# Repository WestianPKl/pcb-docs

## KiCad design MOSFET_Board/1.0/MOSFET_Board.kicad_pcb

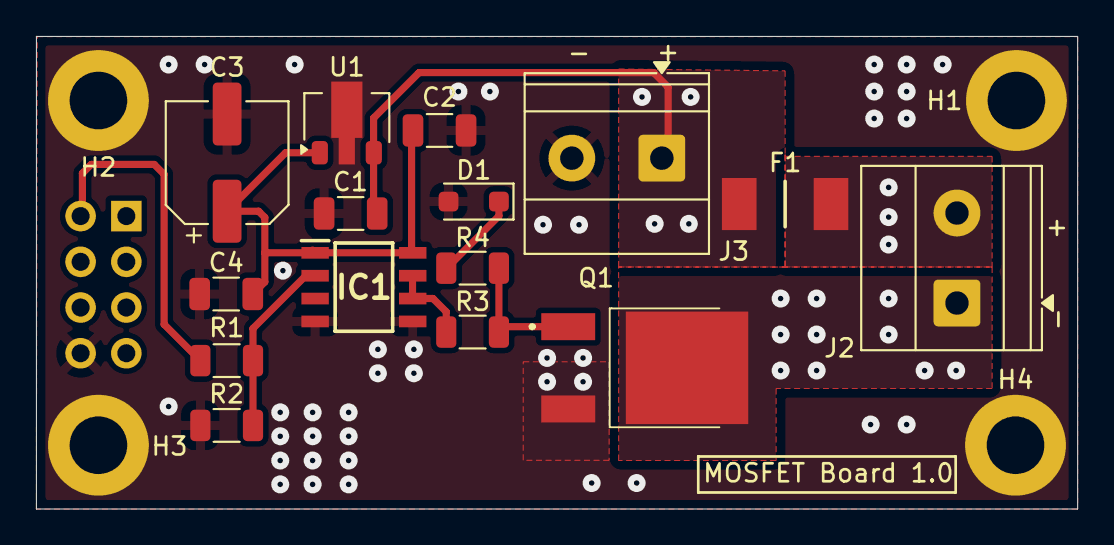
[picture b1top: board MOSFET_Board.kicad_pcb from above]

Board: 2 copper layers, 57.8 x 26.3 mm, 20 parts (1 on the bottom side), 10 nets.

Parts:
C1: 330nF; C_1206_3216Metric
C2, C4: 100nF; C_1206_3216Metric
C3: 10uF; CP_Elec_6.3x5.8
D1: BZT52C15-DIO; D_SOD-123F
F1: TR1-2410TD5-R; FUSC6127X287N
H1, H2, H3, H4: MountingHole_Pad; MountingHole_3.2mm_M3_DIN965_Pad
IC1: TC4420EOA; SOIC127P600X175-8N
J1: COM; PinHeader_2x04_P2.54mm_Vertical
J2: BULB; TerminalBlock_Phoenix_MKDS-1,5-2_1x02_P5.00mm_Horizontal
J3: PWR; TerminalBlock_Phoenix_MKDS-1,5-2_1x02_P5.00mm_Horizontal
Q1: AOD4184A; AOD4185
R1: 100R; R_1206_3216Metric
R2: 47K; R_1206_3216Metric
R3: 10R; R_1206_3216Metric
R4: 100K; R_1206_3216Metric
U1: L78L12ABUTR; SOT-89-3

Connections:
+12V: C1.1, F1.2, J3.1, U1.3 (IN)
+12V_STAB: C2.1, C3.1, C4.1, IC1.1 (VDD_1), IC1.8 (VDD_2), U1.1 (OUT)
GND: C1.2, C2.2, C3.2, C4.2, D1.2 (A), H1.1, H2.1, H3.1, H4.1, IC1.4 (GND_1), IC1.5 (GND_2), J1.8, J3.2, Q1.3 (S), R2.2, U1.2 (GND)
unnamed: D1.1 (K), R4.2
unnamed: IC1.2 (INPUT), R1.2, R2.1
unnamed: IC1.6 (OUTPUT_1), IC1.7 (OUTPUT_2), R3.1
unnamed: J1.2, R1.1
unnamed: J2.1, Q1.2 (D)
unnamed: F1.1, J2.2
unnamed: Q1.1 (G), R3.2, R4.1

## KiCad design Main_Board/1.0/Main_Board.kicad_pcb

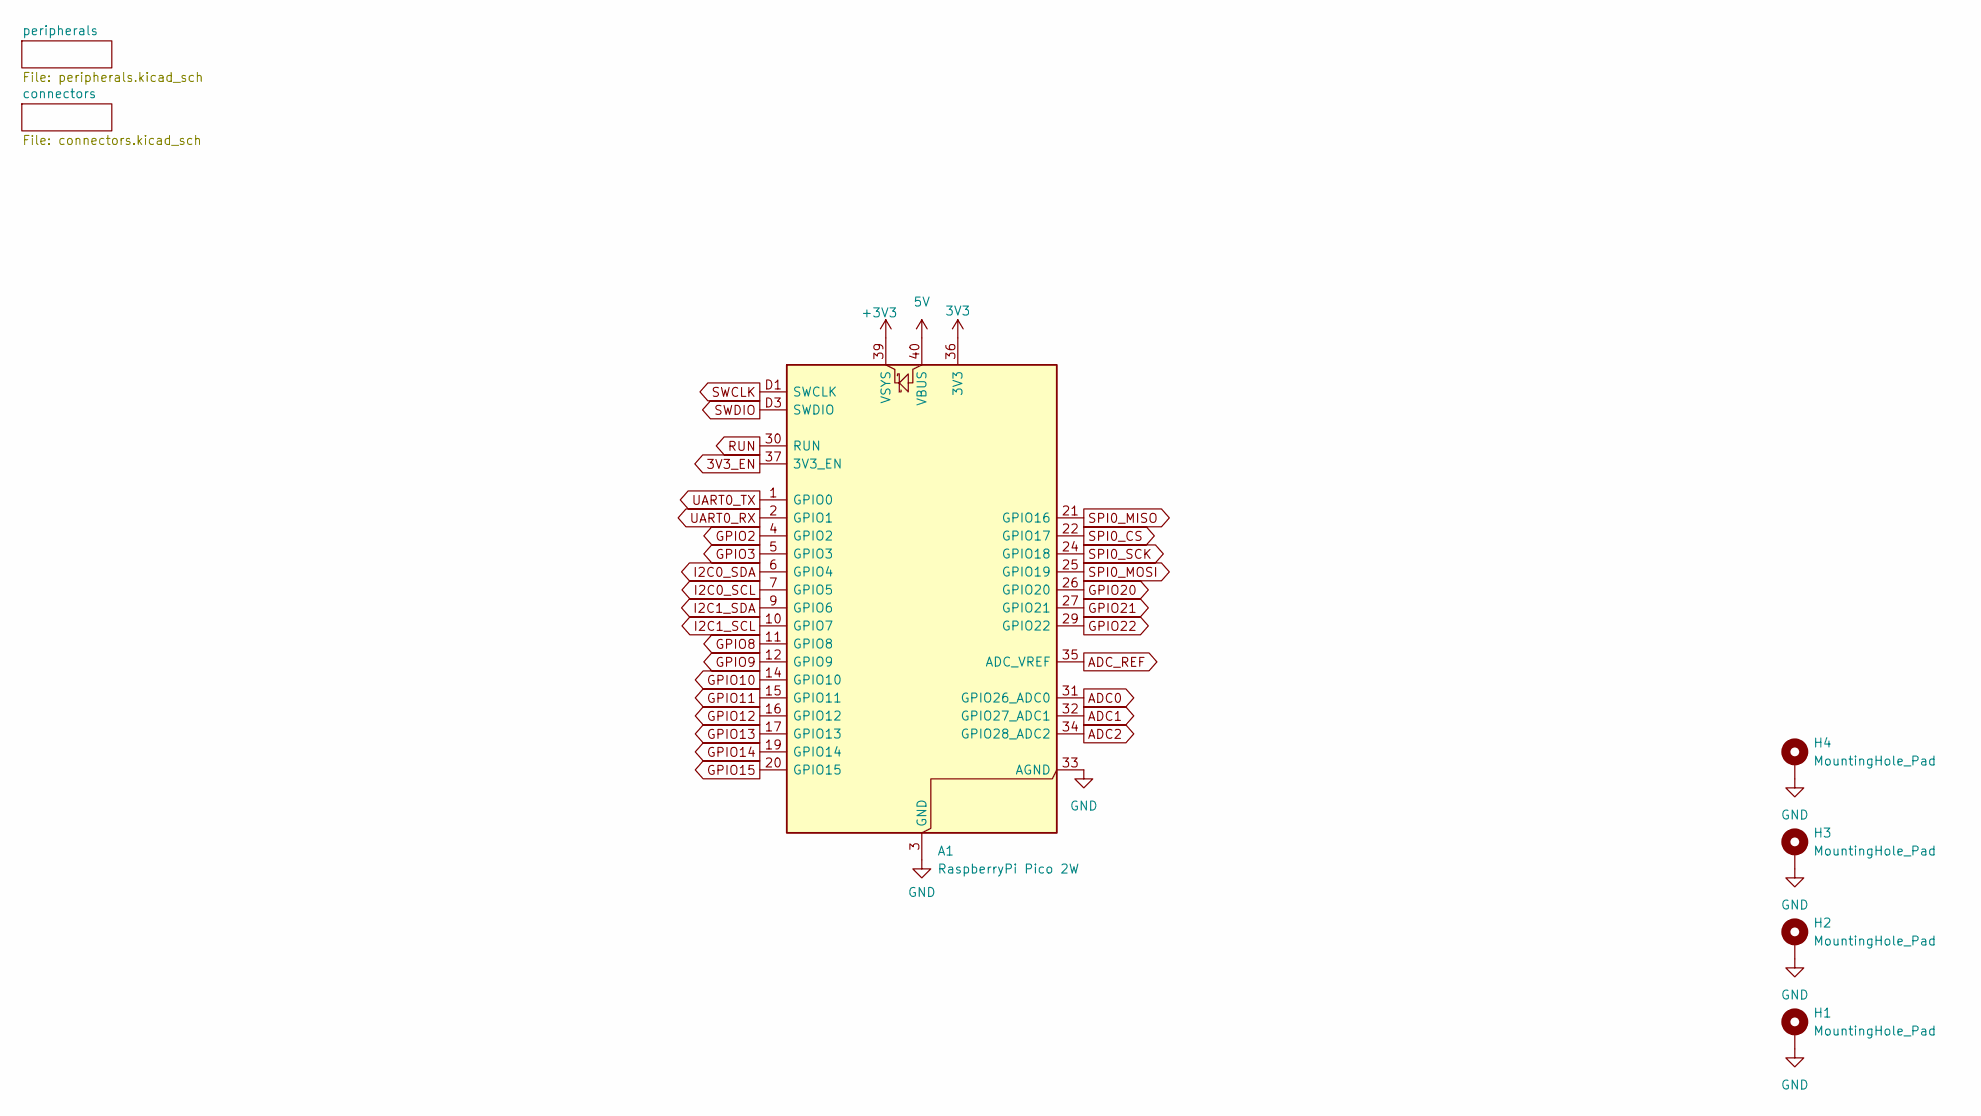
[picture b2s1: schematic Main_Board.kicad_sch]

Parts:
A1: RaspberryPi Pico 2W; RaspberryPi_Pico_Common_Unspecified
H1, H2, H3, H4: MountingHole_Pad; MountingHole_3.2mm_M3_DIN965_Pad

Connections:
3V3: A1.36 (3V3); also elsewhere on the board
3V3_EN: A1.37 (3V3_EN); also elsewhere on the board
5V: A1.40 (VBUS); also elsewhere on the board
+3V3: A1.39 (VSYS); also elsewhere on the board
ADC0: A1.31 (GPIO26_ADC0); also elsewhere on the board
ADC1: A1.32 (GPIO27_ADC1); also elsewhere on the board
ADC2: A1.34 (GPIO28_ADC2); also elsewhere on the board
ADC_REF: A1.35 (ADC_VREF); also elsewhere on the board
GND: A1.3 (GND), A1.8 (GND), A1.13 (GND), A1.18 (GND), A1.23 (GND), A1.28 (GND), A1.33 (AGND), A1.38 (GND), A1.D2 (GND), H1.1, H2.1, H3.1, H4.1; also elsewhere on the board
GPIO2: A1.4 (GPIO2); also elsewhere on the board
GPIO3: A1.5 (GPIO3); also elsewhere on the board
GPIO8: A1.11 (GPIO8); also elsewhere on the board
GPIO9: A1.12 (GPIO9); also elsewhere on the board
GPIO10: A1.14 (GPIO10); also elsewhere on the board
GPIO11: A1.15 (GPIO11); also elsewhere on the board
GPIO12: A1.16 (GPIO12); also elsewhere on the board
GPIO13: A1.17 (GPIO13); also elsewhere on the board
GPIO14: A1.19 (GPIO14); also elsewhere on the board
GPIO15: A1.20 (GPIO15); also elsewhere on the board
GPIO20: A1.26 (GPIO20); also elsewhere on the board
GPIO21: A1.27 (GPIO21); also elsewhere on the board
GPIO22: A1.29 (GPIO22); also elsewhere on the board
I2C0_SCL: A1.7 (GPIO5); also elsewhere on the board
I2C0_SDA: A1.6 (GPIO4); also elsewhere on the board
I2C1_SCL: A1.10 (GPIO7); also elsewhere on the board
I2C1_SDA: A1.9 (GPIO6); also elsewhere on the board
RUN: A1.30 (RUN); also elsewhere on the board
SPI0_CS: A1.22 (GPIO17); also elsewhere on the board
SPI0_MISO: A1.21 (GPIO16); also elsewhere on the board
SPI0_MOSI: A1.25 (GPIO19); also elsewhere on the board
SPI0_SCK: A1.24 (GPIO18); also elsewhere on the board
SWCLK: A1.D1 (SWCLK); also elsewhere on the board
SWDIO: A1.D3 (SWDIO); also elsewhere on the board
UART0_RX: A1.2 (GPIO1); also elsewhere on the board
UART0_TX: A1.1 (GPIO0); also elsewhere on the board

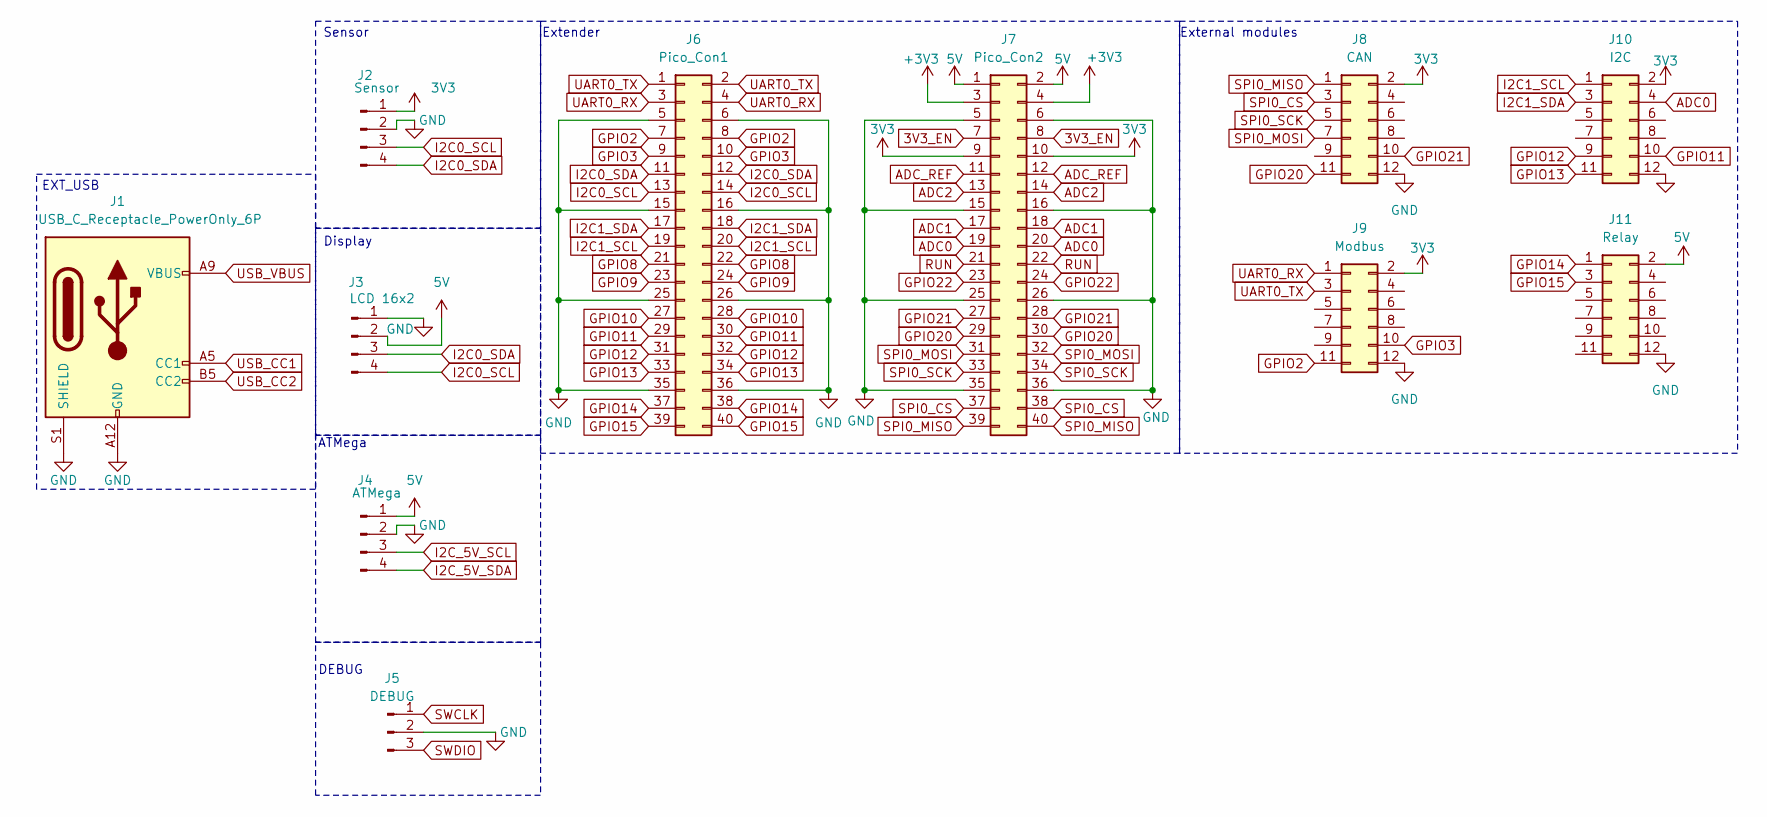
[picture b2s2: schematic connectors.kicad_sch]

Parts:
J1: USB_C_Receptacle_PowerOnly_6P; USB_C_Receptacle_GCT_USB4125-xx-x_6P_TopMnt_Horizontal
J2: Sensor; JST_XH_B4B-XH-A_1x04_P2.50mm_Vertical
J3: LCD 16x2; JST_XH_B4B-XH-A_1x04_P2.50mm_Vertical
J4: ATMega; PinHeader_1x04_P2.54mm_Vertical
J5: DEBUG; JST_XH_B3B-XH-A_1x03_P2.50mm_Vertical
J6: Pico_Con1; PinHeader_2x20_P2.54mm_Vertical
J7: Pico_Con2; PinHeader_2x20_P2.54mm_Vertical
J8: CAN; PinSocket_2x06_P2.54mm_Vertical
J9: Modbus; PinSocket_2x06_P2.54mm_Vertical
J10: I2C; PinSocket_2x06_P2.54mm_Vertical
J11: Relay; PinSocket_2x06_P2.54mm_Vertical

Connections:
3V3: J2.1, J7.9, J7.10, J8.2, J9.2, J10.2; also elsewhere on the board
3V3_EN: J7.7, J7.8; also elsewhere on the board
5V: J3.2, J4.1, J7.1, J7.2, J11.2; also elsewhere on the board
+3V3: J7.3, J7.4; also elsewhere on the board
ADC0: J7.19, J7.20, J10.4; also elsewhere on the board
ADC1: J7.17, J7.18; also elsewhere on the board
ADC2: J7.13, J7.14; also elsewhere on the board
ADC_REF: J7.11, J7.12; also elsewhere on the board
GND: J1.A12 (GND), J1.B12 (GND), J1.S1 (SHIELD), J2.2, J3.1, J4.2, J5.2, J6.5, J6.6, J6.15, J6.16, J6.25, J6.26, J6.35, J6.36, J7.5, J7.6, J7.15, J7.16, J7.25, J7.26, J7.35, J7.36, J8.12, J9.12, J10.12, J11.12; also elsewhere on the board
GPIO2: J6.7, J6.8, J9.11; also elsewhere on the board
GPIO3: J6.9, J6.10, J9.10; also elsewhere on the board
GPIO8: J6.21, J6.22; also elsewhere on the board
GPIO9: J6.23, J6.24; also elsewhere on the board
GPIO10: J6.27, J6.28; also elsewhere on the board
GPIO11: J6.29, J6.30, J10.10; also elsewhere on the board
GPIO12: J6.31, J6.32, J10.9; also elsewhere on the board
GPIO13: J6.33, J6.34, J10.11; also elsewhere on the board
GPIO14: J6.37, J6.38, J11.1; also elsewhere on the board
GPIO15: J6.39, J6.40, J11.3; also elsewhere on the board
GPIO20: J7.29, J7.30, J8.11; also elsewhere on the board
GPIO21: J7.27, J7.28, J8.10; also elsewhere on the board
GPIO22: J7.23, J7.24; also elsewhere on the board
I2C0_SCL: J2.3, J3.4, J6.13, J6.14; also elsewhere on the board
I2C0_SDA: J2.4, J3.3, J6.11, J6.12; also elsewhere on the board
I2C1_SCL: J6.19, J6.20, J10.1; also elsewhere on the board
I2C1_SDA: J6.17, J6.18, J10.3; also elsewhere on the board
I2C_5V_SCL: J4.3; also elsewhere on the board
I2C_5V_SDA: J4.4; also elsewhere on the board
RUN: J7.21, J7.22; also elsewhere on the board
SPI0_CS: J7.37, J7.38, J8.3; also elsewhere on the board
SPI0_MISO: J7.39, J7.40, J8.1; also elsewhere on the board
SPI0_MOSI: J7.31, J7.32, J8.7; also elsewhere on the board
SPI0_SCK: J7.33, J7.34, J8.5; also elsewhere on the board
SWCLK: J5.1; also elsewhere on the board
SWDIO: J5.3; also elsewhere on the board
UART0_RX: J6.3, J6.4, J9.1; also elsewhere on the board
UART0_TX: J6.1, J6.2, J9.3; also elsewhere on the board
USB_CC1: J1.A5 (CC1); also elsewhere on the board
USB_CC2: J1.B5 (CC2); also elsewhere on the board
USB_VBUS: J1.A9 (VBUS), J1.B9 (VBUS); also elsewhere on the board

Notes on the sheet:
ATMega
Sensor
Extender
Display
External modules
EXT_USB
DEBUG

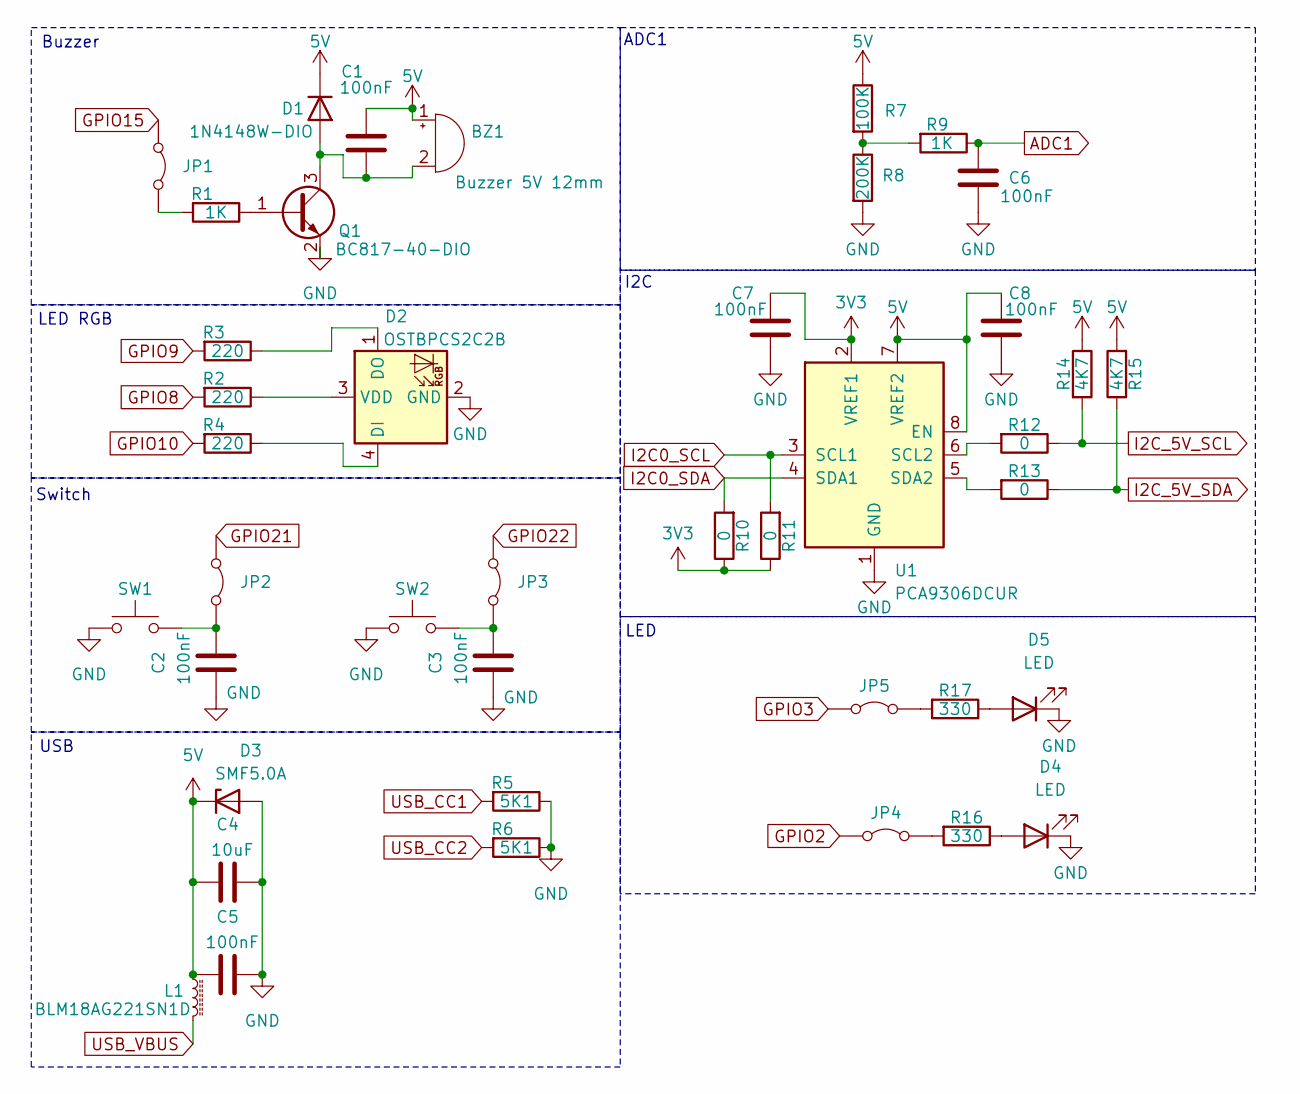
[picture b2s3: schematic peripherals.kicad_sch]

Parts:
BZ1: Buzzer 5V 12mm; Buzzer_12x9.5RM7.6
C1, C2, C3, C5, C6, C7, C8: 100nF; C_0805_2012Metric
C4: 10uF; C_0805_2012Metric
D1: 1N4148W-DIO; D_SOD-123F
D2: OSTBPCS2C2B; LED_Avago_PLCC4_3.2x2.8mm_CW
D3: SMF5.0A; D_SOD-123F
D4, D5: LED; LED_0805_2012Metric
JP1, JP2, JP3, JP4, JP5: Jumper_2_Bridged; PinHeader_1x02_P2.54mm_Vertical
L1: BLM18AG221SN1D; L_0603_1608Metric
Q1: BC817-40-DIO; SOT-23
R1, R9: 1K; R_0805_2012Metric
R2, R3, R4: 220; R_0805_2012Metric
R5, R6: 5K1; R_0805_2012Metric
R7: 100K; R_0805_2012Metric
R8: 200K; R_0805_2012Metric
R10, R11, R12, R13: 0; R_0805_2012Metric
R14, R15: 4K7; R_0805_2012Metric
R16, R17: 330; R_0805_2012Metric
SW1, SW2: Tact Switch 6x6mm / 13mm; SW_PUSH_6mm
U1: PCA9306DCUR; VSSOP-8_2.3x2mm_P0.5mm

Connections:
3V3: C7.1, R10.1, R11.1, U1.2 (VREF1); also elsewhere on the board
5V: BZ1.1 (+), C1.2, C4.2, C5.2, C8.1, D1.1 (K), D3.1 (K), L1.1, R7.1, R14.1, R15.2, U1.7 (VREF2), U1.8 (EN); also elsewhere on the board
ADC1: C6.1, R9.1; also elsewhere on the board
GND: C2.2, C3.2, C4.1, C5.1, C6.2, C7.2, C8.2, D2.2 (GND), D3.2 (A), D4.1 (K), D5.1 (K), Q1.2 (E), R5.1, R6.1, R8.2, SW1.1, SW2.1, U1.1 (GND); also elsewhere on the board
GPIO2: JP4.1 (A); also elsewhere on the board
GPIO3: JP5.1 (A); also elsewhere on the board
GPIO8: R2.2; also elsewhere on the board
GPIO9: R3.2; also elsewhere on the board
GPIO10: R4.2; also elsewhere on the board
GPIO15: JP1.1 (A); also elsewhere on the board
GPIO21: JP2.1 (A); also elsewhere on the board
GPIO22: JP3.1 (A); also elsewhere on the board
I2C0_SCL: R11.2, U1.3 (SCL1); also elsewhere on the board
I2C0_SDA: R10.2, U1.4 (SDA1); also elsewhere on the board
I2C_5V_SCL: R12.1, R14.2; also elsewhere on the board
I2C_5V_SDA: R13.1, R15.1; also elsewhere on the board
unnamed: BZ1.2 (-), C1.1, D1.2 (A), Q1.3 (C)
unnamed: D2.4 (DI), R4.1
unnamed: D2.1 (DO), R3.1
unnamed: D2.3 (VDD), R2.1
unnamed: D4.2 (A), R16.1
unnamed: D5.2 (A), R17.1
unnamed: JP1.2 (B), R1.2
unnamed: C2.1, JP2.2 (B), SW1.2
unnamed: C3.1, JP3.2 (B), SW2.2
unnamed: JP4.2 (B), R16.2
unnamed: JP5.2 (B), R17.2
unnamed: Q1.1 (B), R1.1
unnamed: R7.2, R8.1, R9.2
unnamed: R12.2, U1.6 (SCL2)
unnamed: R13.2, U1.5 (SDA2)
USB_CC1: R5.2; also elsewhere on the board
USB_CC2: R6.2; also elsewhere on the board
USB_VBUS: L1.2; also elsewhere on the board

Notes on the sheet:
I2C
LED RGB
USB
LED
ADC1
Buzzer
Switch

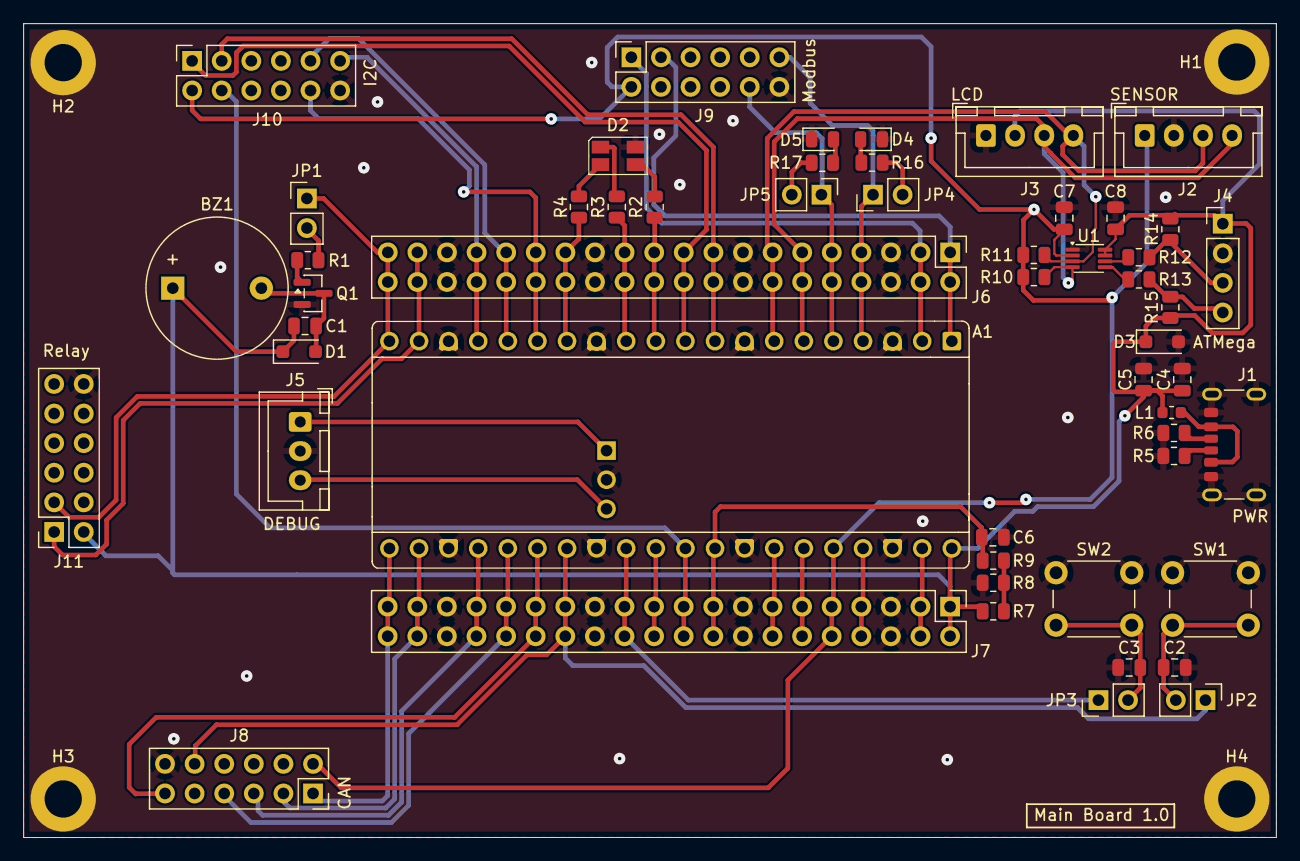
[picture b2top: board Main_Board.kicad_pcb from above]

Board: 2 copper layers, 107.5 x 69.8 mm, 57 parts (0 on the bottom side), 55 nets.

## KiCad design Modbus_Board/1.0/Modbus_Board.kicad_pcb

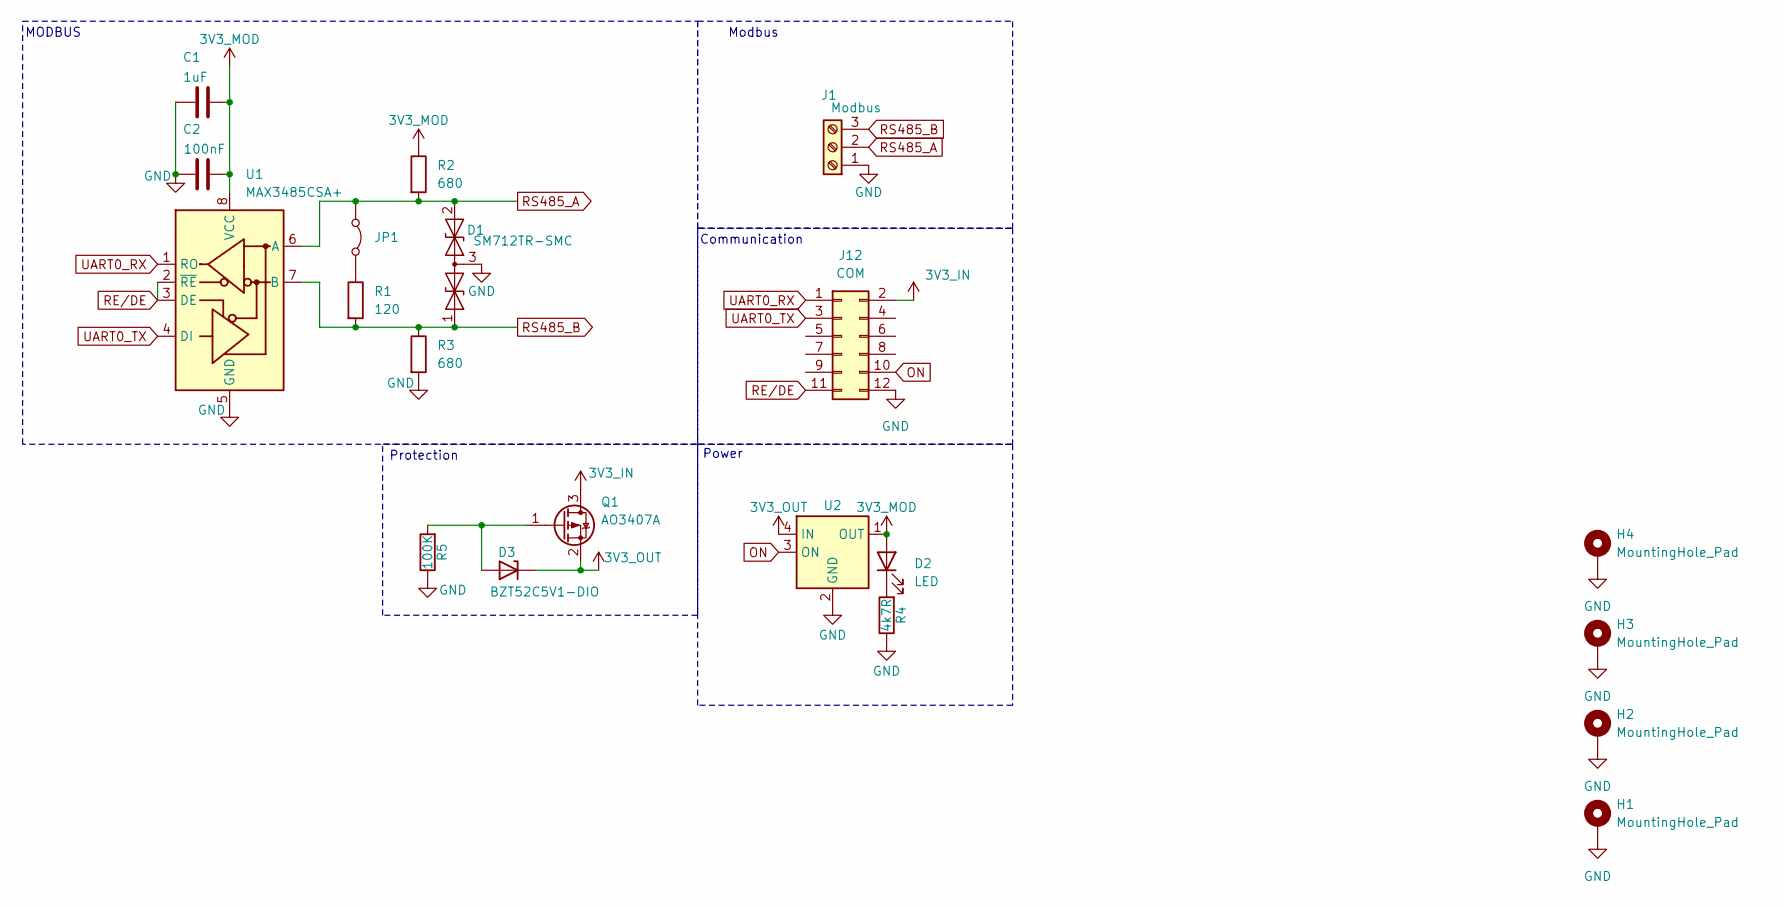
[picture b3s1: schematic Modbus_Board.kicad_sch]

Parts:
C1: 1uF; C_0603_1608Metric
C2: 100nF; C_0805_2012Metric
D1: SM712TR-SMC; SOT-23
D2: LED; LED_0805_2012Metric
D3: BZT52C5V1-DIO; D_SOD-123F
H1, H2, H3, H4: MountingHole_Pad; MountingHole_3.2mm_M3_DIN965_Pad
J1: Modbus; TerminalBlock_Phoenix_MKDS-1,5-3_1x03_P5.00mm_Horizontal
J12: COM; PinHeader_2x06_P2.54mm_Vertical
JP1: Jumper_2_Bridged; PinHeader_1x02_P2.54mm_Vertical
Q1: AO3407A; SOT-23
R1: 120; R_0805_2012Metric
R2, R3: 680; R_0805_2012Metric
R4: 4k7R; R_0805_2012Metric
R5: 100K; R_0805_2012Metric
U1: MAX3485CSA+; SOIC-8_3.9x4.9mm_P1.27mm
U2: SIP32431DR3-T1GE3; SOT-363_SC-70-6

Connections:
3V3_IN: J12.2, Q1.3 (D)
3V3_MOD: C1.1, C2.1, D2.2 (A), R2.1, U1.8 (VCC), U2.1 (OUT)
3V3_OUT: D3.1 (K), Q1.2 (S), U2.4 (IN)
GND: C1.2, C2.2, D1.3 (common), H1.1, H2.1, H3.1, H4.1, J1.1, J12.12, R3.2, R4.1, R5.1, U1.5 (GND), U2.2 (GND), U2.5 (GND)
unnamed: D2.1 (K), R4.2
unnamed: D3.2 (A), Q1.1 (G), R5.2
unnamed: JP1.2 (B), R1.1
ON: J12.10, U2.3 (ON)
RE/DE: J12.11, U1.2 (~RE), U1.3 (DE)
RS485_A: D1.2 (A2), J1.2, JP1.1 (A), R2.2, U1.6 (A)
RS485_B: D1.1 (A1), J1.3, R1.2, R3.1, U1.7 (B)
UART0_RX: J12.1, U1.1 (RO)
UART0_TX: J12.3, U1.4 (DI)

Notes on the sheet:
MODBUS
Power
Protection
Modbus
Communication

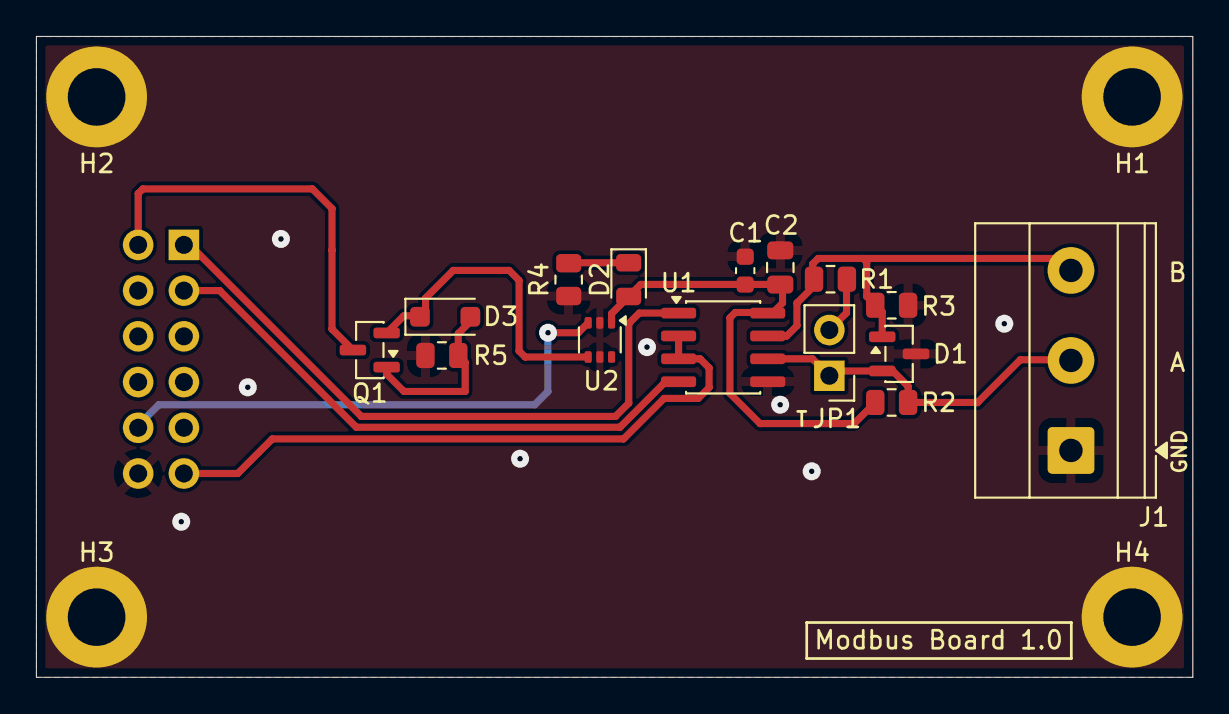
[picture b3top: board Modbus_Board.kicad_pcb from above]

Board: 2 copper layers, 64.2 x 35.6 mm, 20 parts (1 on the bottom side), 13 nets.
